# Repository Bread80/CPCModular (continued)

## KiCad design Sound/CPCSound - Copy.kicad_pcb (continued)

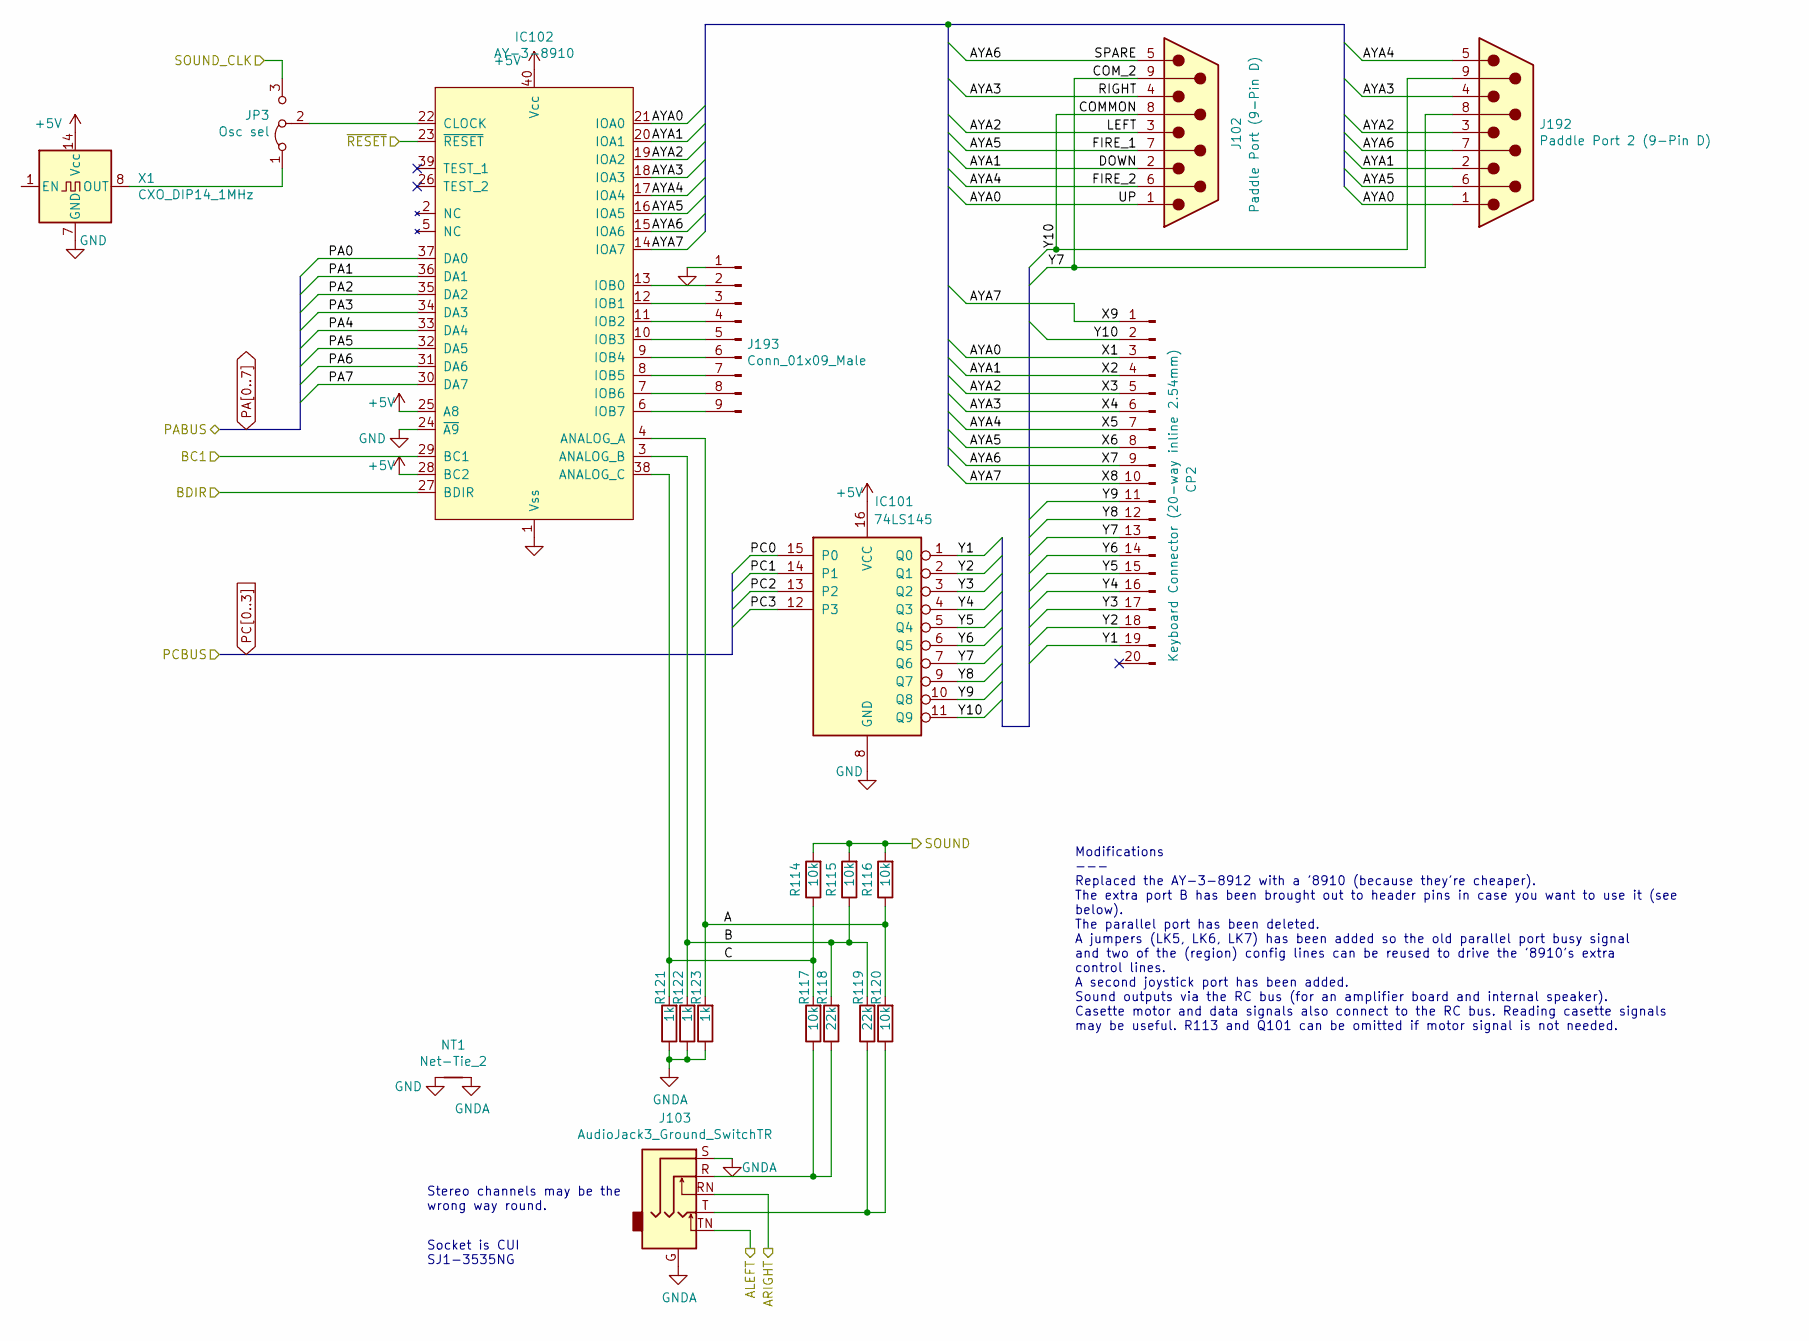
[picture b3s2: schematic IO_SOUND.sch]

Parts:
CP002: Keyboard Connector (20-way inline 2.54mm); PinHeader_1x20_P2.54mm_Vertical
IC101: 74LS145; DIP-16_W7.62mm_Socket
IC102: AY-3-8910; DIP-40_W15.24mm_Socket
J102: Paddle Port (9-Pin D); DSUB-9_Male_Horizontal_P2.77x2.84mm_EdgePinOffset9.90mm_Hou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
J103: AudioJack3_Ground_SwitchTR; Jack_3.5mm_CUI_SJ1-3535NG_Horizontal
J192: Paddle Port 2 (9-Pin D); DSUB-9_Male_Horizontal_P2.77x2.84mm_EdgePinOffset9.40mm
J193: Conn_01x09_Male; PinHeader_1x09_P2.54mm_Vertical
JP3: Osc sel; PinHeader_1x03_P2.54mm_Vertical
NT1: Net-Tie_2; NetTie-2_SMD_Pad0.5mm
R114, R115, R116, R117, R120: 10k; R_Axial_DIN0207_L6.3mm_D2.5mm_P7.62mm_Horizontal
R118, R119: 22k; R_Axial_DIN0207_L6.3mm_D2.5mm_P7.62mm_Horizontal
R121, R122, R123: 1k; R_Axial_DIN0207_L6.3mm_D2.5mm_P7.62mm_Horizontal
X1: CXO_DIP14_1MHz; Oscillator_DIP-14

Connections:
+5V: IC101.16 (VCC), IC102.25 (A8), IC102.28 (BC2), IC102.40 (Vcc), X1.14 (Vcc); also elsewhere on the board
/IO_SOUND/A: IC102.4 (ANALOG_A), R116.1, R120.2, R123.2
/IO_SOUND/ALEFT: J103.TN; also elsewhere on the board
/IO_SOUND/ARIGHT: J103.RN; also elsewhere on the board
/IO_SOUND/AYA0: IC102.21 (IOA0), J102.1, J192.1; also elsewhere on the board
/IO_SOUND/AYA1: IC102.20 (IOA1), J102.2, J192.2; also elsewhere on the board
/IO_SOUND/AYA2: IC102.19 (IOA2), J102.3, J192.3; also elsewhere on the board
/IO_SOUND/AYA3: IC102.18 (IOA3), J102.4, J192.4; also elsewhere on the board
/IO_SOUND/AYA4: IC102.17 (IOA4), J102.6, J192.5; also elsewhere on the board
/IO_SOUND/AYA5: IC102.16 (IOA5), J102.7, J192.6; also elsewhere on the board
/IO_SOUND/AYA6: IC102.15 (IOA6), J102.5, J192.7; also elsewhere on the board
/IO_SOUND/AYA7: IC102.14 (IOA7); also elsewhere on the board
/IO_SOUND/B: IC102.3 (ANALOG_B), R115.1, R118.2, R119.2, R122.2
/IO_SOUND/BC1: IC102.29 (BC1); also elsewhere on the board
/IO_SOUND/BDIR: IC102.27 (BDIR); also elsewhere on the board
/IO_SOUND/C: IC102.38 (ANALOG_C), R114.1, R117.2, R121.2
/IO_SOUND/COMMON: IC101.11 (Q9), J102.8, J192.9; also elsewhere on the board
/IO_SOUND/COM_2: IC101.7 (Q6), J102.9, J192.8; also elsewhere on the board
/IO_SOUND/SOUND: R114.2, R115.2, R116.2; also elsewhere on the board
/IO_SOUND/SOUND_CLK: JP3.3 (B); also elsewhere on the board
/IO_SOUND/Y1: IC101.1 (Q0); also elsewhere on the board
/IO_SOUND/Y2: IC101.2 (Q1); also elsewhere on the board
/IO_SOUND/Y3: IC101.3 (Q2); also elsewhere on the board
/IO_SOUND/Y4: IC101.4 (Q3); also elsewhere on the board
/IO_SOUND/Y5: IC101.5 (Q4); also elsewhere on the board
/IO_SOUND/Y6: IC101.6 (Q5); also elsewhere on the board
/IO_SOUND/Y8: IC101.9 (Q7); also elsewhere on the board
/IO_SOUND/Y9: IC101.10 (Q8); also elsewhere on the board
/IO_SOUND/~RESET: IC102.23 (~RESET); also elsewhere on the board
GND: IC101.8 (GND), IC102.1 (Vss), IC102.24 (~A9), J193.1, NT1.1, X1.7 (GND); also elsewhere on the board
GNDA: J103.G, J103.S, NT1.2, R121.1, R122.1, R123.1
unnamed: IC102.6 (IOB7), J193.9
unnamed: IC102.7 (IOB6), J193.8
unnamed: IC102.8 (IOB5), J193.7
unnamed: IC102.9 (IOB4), J193.6
unnamed: IC102.10 (IOB3), J193.5
unnamed: IC102.11 (IOB2), J193.4
unnamed: IC102.12 (IOB1), J193.3
unnamed: IC102.13 (IOB0), J193.2
unnamed: IC102.22 (CLOCK), JP3.2 (C)
unnamed: J103.R, R117.1, R118.1
unnamed: J103.T, R119.1, R120.1
unnamed: JP3.1 (A), X1.8 (OUT)
PA0: IC102.37 (DA0); also elsewhere on the board
PA1: IC102.36 (DA1); also elsewhere on the board
PA2: IC102.35 (DA2); also elsewhere on the board
PA3: IC102.34 (DA3); also elsewhere on the board
PA4: IC102.33 (DA4); also elsewhere on the board
PA5: IC102.32 (DA5); also elsewhere on the board
PA6: IC102.31 (DA6); also elsewhere on the board
PA7: IC102.30 (DA7); also elsewhere on the board
PC0: IC101.15 (P0); also elsewhere on the board
PC1: IC101.14 (P1); also elsewhere on the board
PC2: IC101.13 (P2); also elsewhere on the board
PC3: IC101.12 (P3); also elsewhere on the board

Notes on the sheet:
Modifications --- Replaced the AY-3-8912 with a '8910 (because they're cheaper). The extra port B has been brought out to header pins in case you want to use it (see below). The parallel port has been deleted. A jumpers (LK5, LK6, LK7) has been added so the old parallel port busy signal and two of 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
Stereo channels may be the wrong way round.
Socket is CUI SJ1-3535NG

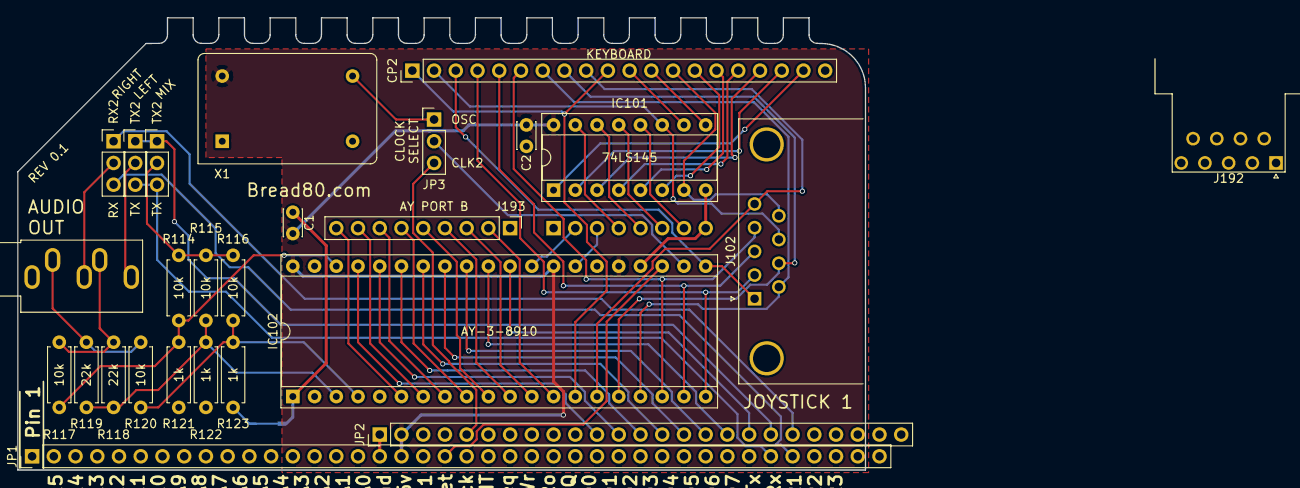
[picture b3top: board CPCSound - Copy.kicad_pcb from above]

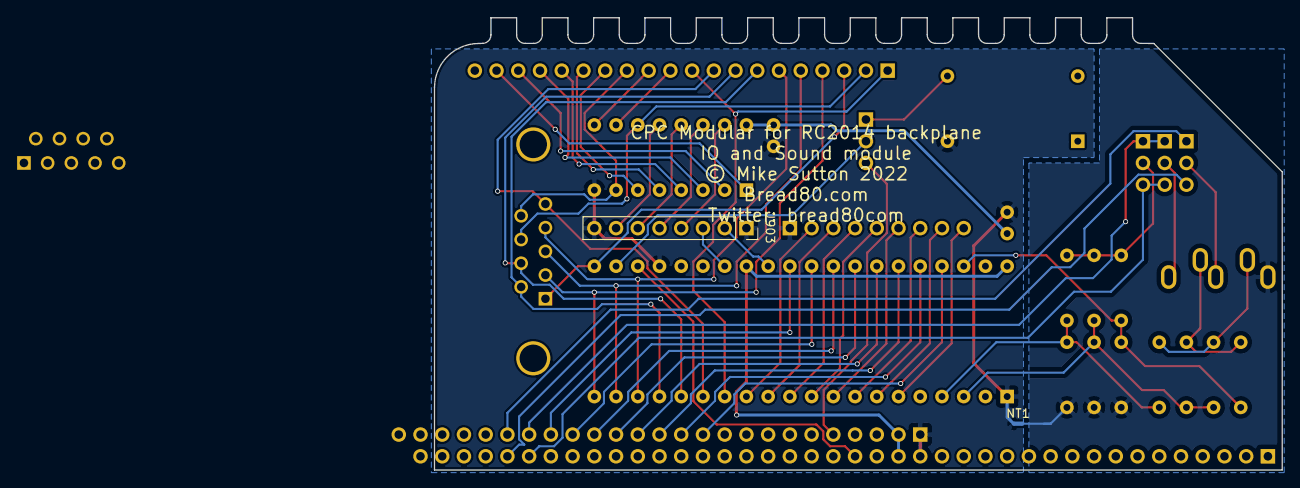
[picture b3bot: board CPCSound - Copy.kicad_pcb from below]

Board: 2 copper layers, 99.1 x 52.9 mm, 28 parts (2 on the bottom side), 59 nets.

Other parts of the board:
CP2: Keyboard Connector (20-way inline 2.54mm); PinHeader_1x20_P2.54mm_Vertical

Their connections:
/IO_SOUND/AYA0: CP2.3; also elsewhere on the board
/IO_SOUND/AYA1: CP2.4; also elsewhere on the board
/IO_SOUND/AYA2: CP2.5; also elsewhere on the board
/IO_SOUND/AYA3: CP2.6; also elsewhere on the board
/IO_SOUND/AYA4: CP2.7; also elsewhere on the board
/IO_SOUND/AYA5: CP2.8; also elsewhere on the board
/IO_SOUND/AYA6: CP2.9; also elsewhere on the board
/IO_SOUND/AYA7: CP2.1, CP2.10; also elsewhere on the board
/IO_SOUND/COMMON: CP2.2; also elsewhere on the board
/IO_SOUND/COM_2: CP2.13; also elsewhere on the board
/IO_SOUND/Y1: CP2.19; also elsewhere on the board
/IO_SOUND/Y2: CP2.18; also elsewhere on the board
/IO_SOUND/Y3: CP2.17; also elsewhere on the board
/IO_SOUND/Y4: CP2.16; also elsewhere on the board
/IO_SOUND/Y5: CP2.15; also elsewhere on the board
/IO_SOUND/Y6: CP2.14; also elsewhere on the board
/IO_SOUND/Y8: CP2.12; also elsewhere on the board
/IO_SOUND/Y9: CP2.11; also elsewhere on the board

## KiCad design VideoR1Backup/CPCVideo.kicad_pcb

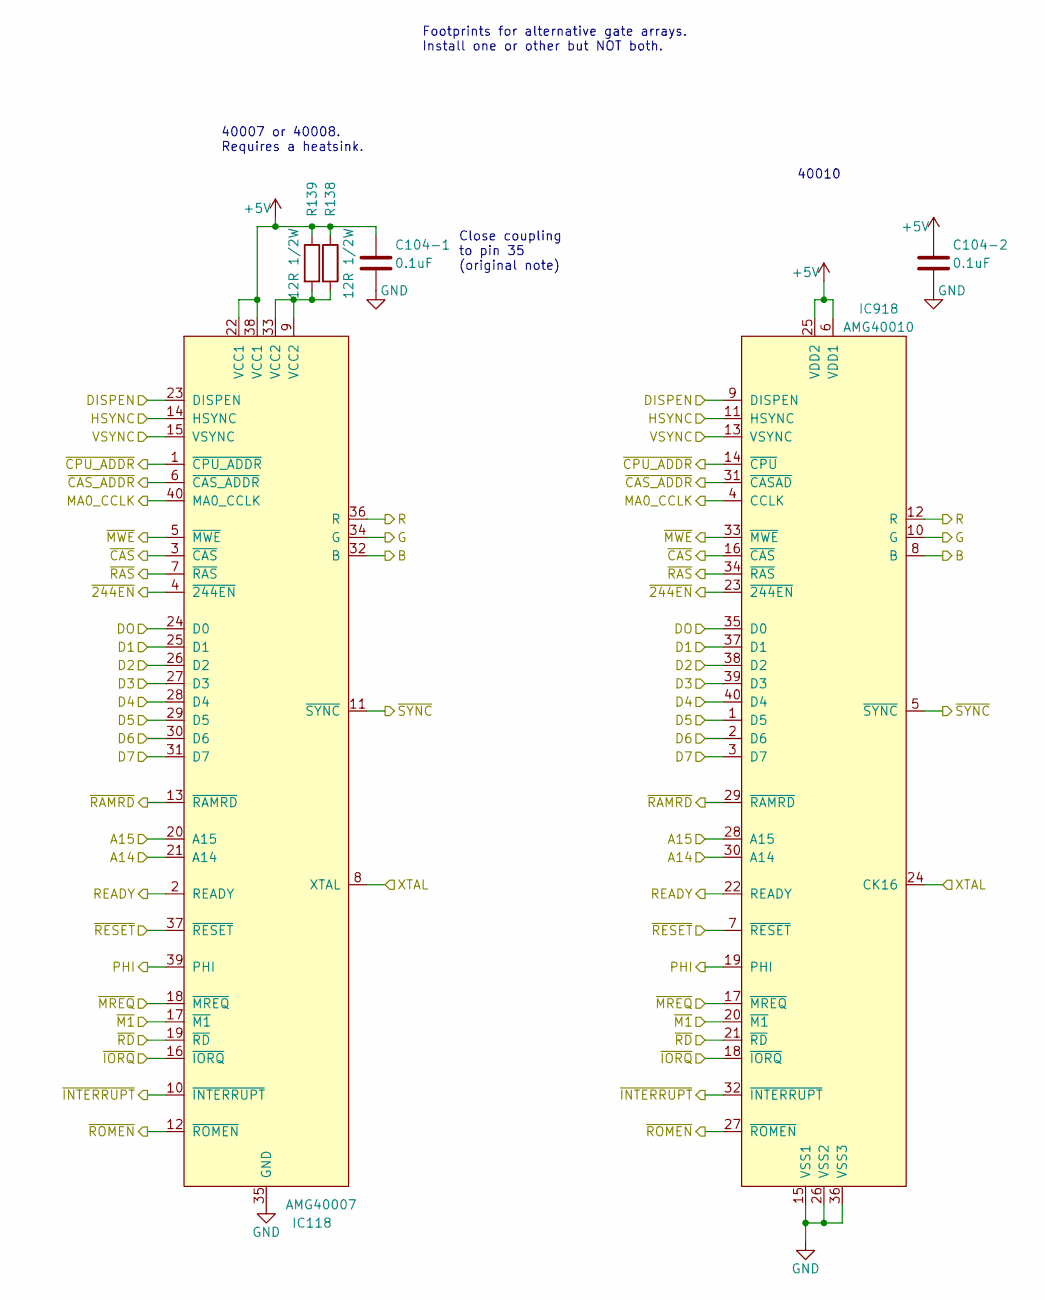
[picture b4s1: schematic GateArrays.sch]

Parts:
C104-1, C104-2: 0.1uF; C_Disc_D3.4mm_W2.1mm_P2.50mm
IC118: AMG40007; DIP-40_W15.24mm_Socket
IC918: AMG40010; DIP-40_W15.24mm_Socket
R138, R139: 12R 1/2W; R_Axial_DIN0309_L9.0mm_D3.2mm_P12.70mm_Horizontal

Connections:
+5V: C104-1.1, C104-2.1, IC118.22 (VCC1), IC118.38 (VCC1), IC918.6 (VDD1), IC918.25 (VDD2), R138.1, R139.1; also elsewhere on the board
/RAM_GA/DISPEN: IC118.23 (DISPEN), IC918.9 (DISPEN); also elsewhere on the board
/RAM_GA/GateArrays/B: IC118.32 (B), IC918.8 (B); also elsewhere on the board
/RAM_GA/GateArrays/G: IC118.34 (G), IC918.10 (G); also elsewhere on the board
/RAM_GA/GateArrays/PHI: IC118.39 (PHI), IC918.19 (PHI); also elsewhere on the board
/RAM_GA/GateArrays/R: IC118.36 (R), IC918.12 (R); also elsewhere on the board
/RAM_GA/GateArrays/XTAL: IC118.8 (XTAL), IC918.24 (CK16); also elsewhere on the board
/RAM_GA/GateArrays/~CAS_ADDR: IC118.6 (~CAS_ADDR), IC918.31 (~CASAD)
/RAM_GA/GateArrays/~SYNC: IC118.11 (~SYNC), IC918.5 (~SYNC); also elsewhere on the board
/RAM_GA/HSYNC: IC118.14 (HSYNC), IC918.11 (HSYNC); also elsewhere on the board
/RAM_GA/MA0_CCLK: IC118.40 (MA0_CCLK), IC918.4 (CCLK); also elsewhere on the board
/RAM_GA/READY: IC118.2 (READY), IC918.22 (READY); also elsewhere on the board
/RAM_GA/VSYNC: IC118.15 (VSYNC), IC918.13 (VSYNC); also elsewhere on the board
/RAM_GA/~244EN: IC118.4 (~244EN), IC918.23 (~244EN); also elsewhere on the board
/RAM_GA/~CAS: IC118.3 (~CAS), IC918.16 (~CAS); also elsewhere on the board
/RAM_GA/~CPU_ADDR: IC118.1 (~CPU_ADDR), IC918.14 (~CPU); also elsewhere on the board
/RAM_GA/~INT: IC118.10 (~INTERRUPT), IC918.32 (~INTERRUPT); also elsewhere on the board
/RAM_GA/~IORQ: IC118.16 (~IORQ), IC918.18 (~IORQ); also elsewhere on the board
/RAM_GA/~M1: IC118.17 (~M1), IC918.20 (~M1); also elsewhere on the board
/RAM_GA/~MREQ: IC118.18 (~MREQ), IC918.17 (~MREQ); also elsewhere on the board
/RAM_GA/~MWE: IC118.5 (~MWE), IC918.33 (~MWE); also elsewhere on the board
/RAM_GA/~RAMRD: IC118.13 (~RAMRD), IC918.29 (~RAMRD); also elsewhere on the board
/RAM_GA/~RAS: IC118.7 (~RAS), IC918.34 (~RAS); also elsewhere on the board
/RAM_GA/~RD: IC118.19 (~RD), IC918.21 (~RD); also elsewhere on the board
/RAM_GA/~RESET: IC118.37 (~RESET), IC918.7 (~RESET); also elsewhere on the board
/RAM_GA/~ROMEN: IC118.12 (~ROMEN), IC918.27 (~ROMEN); also elsewhere on the board
A14: IC118.21 (A14), IC918.30 (A14); also elsewhere on the board
A15: IC118.20 (A15), IC918.28 (A15); also elsewhere on the board
GND: C104-1.2, C104-2.2, IC118.35 (GND), IC918.15 (VSS1), IC918.26 (VSS2), IC918.36 (VSS3); also elsewhere on the board
unnamed: IC118.9 (VCC2), IC118.33 (VCC2), R138.2, R139.2
RD0: IC118.24 (D0), IC918.35 (D0); also elsewhere on the board
RD1: IC118.25 (D1), IC918.37 (D1); also elsewhere on the board
RD2: IC118.26 (D2), IC918.38 (D2); also elsewhere on the board
RD3: IC118.27 (D3), IC918.39 (D3); also elsewhere on the board
RD4: IC118.28 (D4), IC918.40 (D4); also elsewhere on the board
RD5: IC118.29 (D5), IC918.1 (D5); also elsewhere on the board
RD6: IC118.30 (D6), IC918.2 (D6); also elsewhere on the board
RD7: IC118.31 (D7), IC918.3 (D7); also elsewhere on the board

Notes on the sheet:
Close coupling to pin 35 (original note)
40007 or 40008. Requires a heatsink.
40010
Footprints for alternative gate arrays. Install one or other but NOT both.

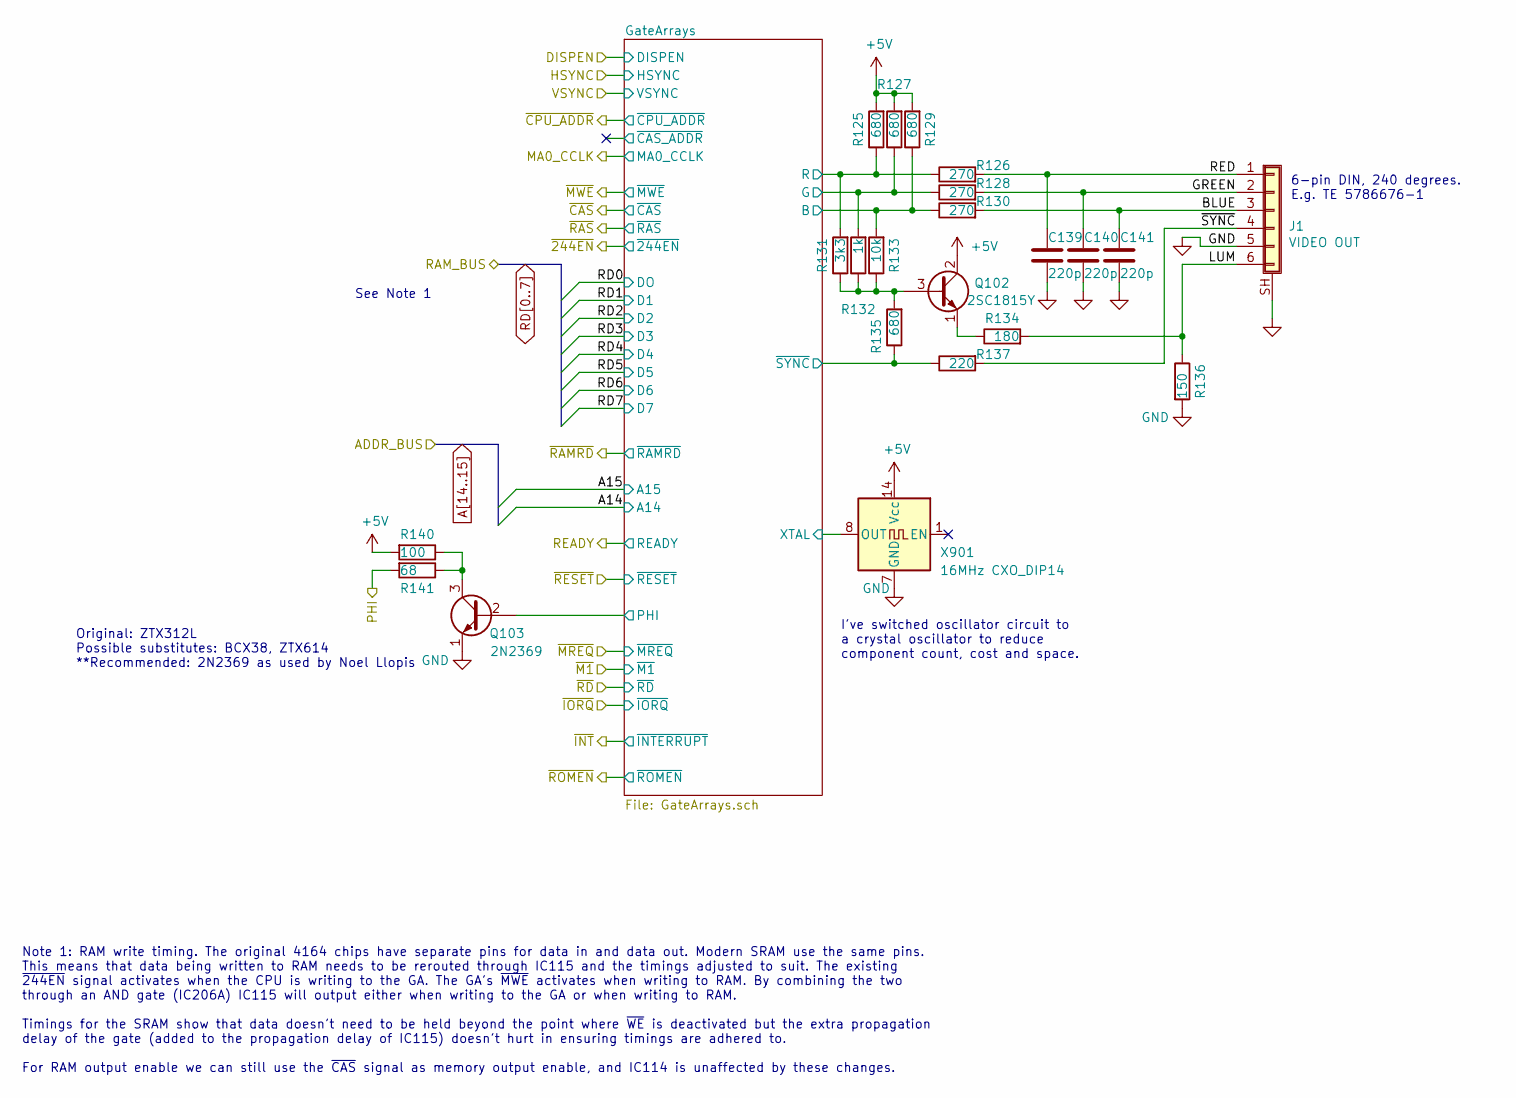
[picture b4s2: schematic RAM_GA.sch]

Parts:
C139, C140, C141: 220p; C_Disc_D3.0mm_W1.6mm_P2.50mm
J1: VIDEO OUT; 6PinDIN240Degree
Q102: 2SC1815Y; TO-92_HandSolder
Q103: 2N2369; TO-18-3
R125, R127, R129, R135: 680; R_Axial_DIN0207_L6.3mm_D2.5mm_P7.62mm_Horizontal
R126, R128, R130: 270; R_Axial_DIN0207_L6.3mm_D2.5mm_P7.62mm_Horizontal
R131: 3k3; R_Axial_DIN0207_L6.3mm_D2.5mm_P7.62mm_Horizontal
R132: 1k; R_Axial_DIN0207_L6.3mm_D2.5mm_P7.62mm_Horizontal
R133: 10k; R_Axial_DIN0207_L6.3mm_D2.5mm_P7.62mm_Horizontal
R134: 180; R_Axial_DIN0207_L6.3mm_D2.5mm_P7.62mm_Horizontal
R136: 150; R_Axial_DIN0207_L6.3mm_D2.5mm_P7.62mm_Horizontal
R137: 220; R_Axial_DIN0207_L6.3mm_D2.5mm_P7.62mm_Horizontal
R140: 100; R_Axial_DIN0207_L6.3mm_D2.5mm_P7.62mm_Horizontal
R141: 68; R_Axial_DIN0207_L6.3mm_D2.5mm_P7.62mm_Horizontal
X201: 16MHz CXO_DIP14; Oscillator_DIP-14

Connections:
+5V: Q102.2 (C), R125.2, R127.2, R129.2, R140.2; also elsewhere on the board
/RAM_GA/BLUE: C141.1, J1.3, R130.2
/RAM_GA/GREEN: C140.1, J1.2, R128.2
/RAM_GA/GateArrays/B: R129.1, R130.1, R133.2; also elsewhere on the board
/RAM_GA/GateArrays/G: R127.1, R128.1, R132.2; also elsewhere on the board
/RAM_GA/GateArrays/PHI: Q103.2 (B); also elsewhere on the board
/RAM_GA/GateArrays/R: R125.1, R126.1, R131.2; also elsewhere on the board
/RAM_GA/GateArrays/~SYNC: R135.1, R137.1; also elsewhere on the board
/RAM_GA/LUM: J1.6, R134.2, R136.1
/RAM_GA/PHI: R141.2; also elsewhere on the board
/RAM_GA/RED: C139.1, J1.1, R126.2
/RAM_GA/~SYNC: J1.4, R137.2
GND: C139.2, C140.2, C141.2, J1.5, J1.SH (Shield), Q103.1 (E), R136.2; also elsewhere on the board
unnamed: Q102.1 (E), R134.1
unnamed: Q102.3 (B), R131.1, R132.1, R133.1, R135.2
unnamed: Q103.3 (C), R140.1, R141.1

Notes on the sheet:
See Note 1
Note 1: RAM write timing. The original 4164 chips have separate pins for data in and data out. Modern SRAM use the same pins. This means that data being written to RAM needs to be rerouted through IC115 and the timings adjusted to suit. The existing ~244EN~ signal activates when the CPU is writing 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
I've switched oscillator circuit to a crystal oscillator to reduce component count, cost and space.
Original: ZTX312L Possible substitutes: BCX38, ZTX614 **Recommended: 2N2369 as used by Noel Llopis
6-pin DIN, 240 degrees. E.g. TE 5786676-1

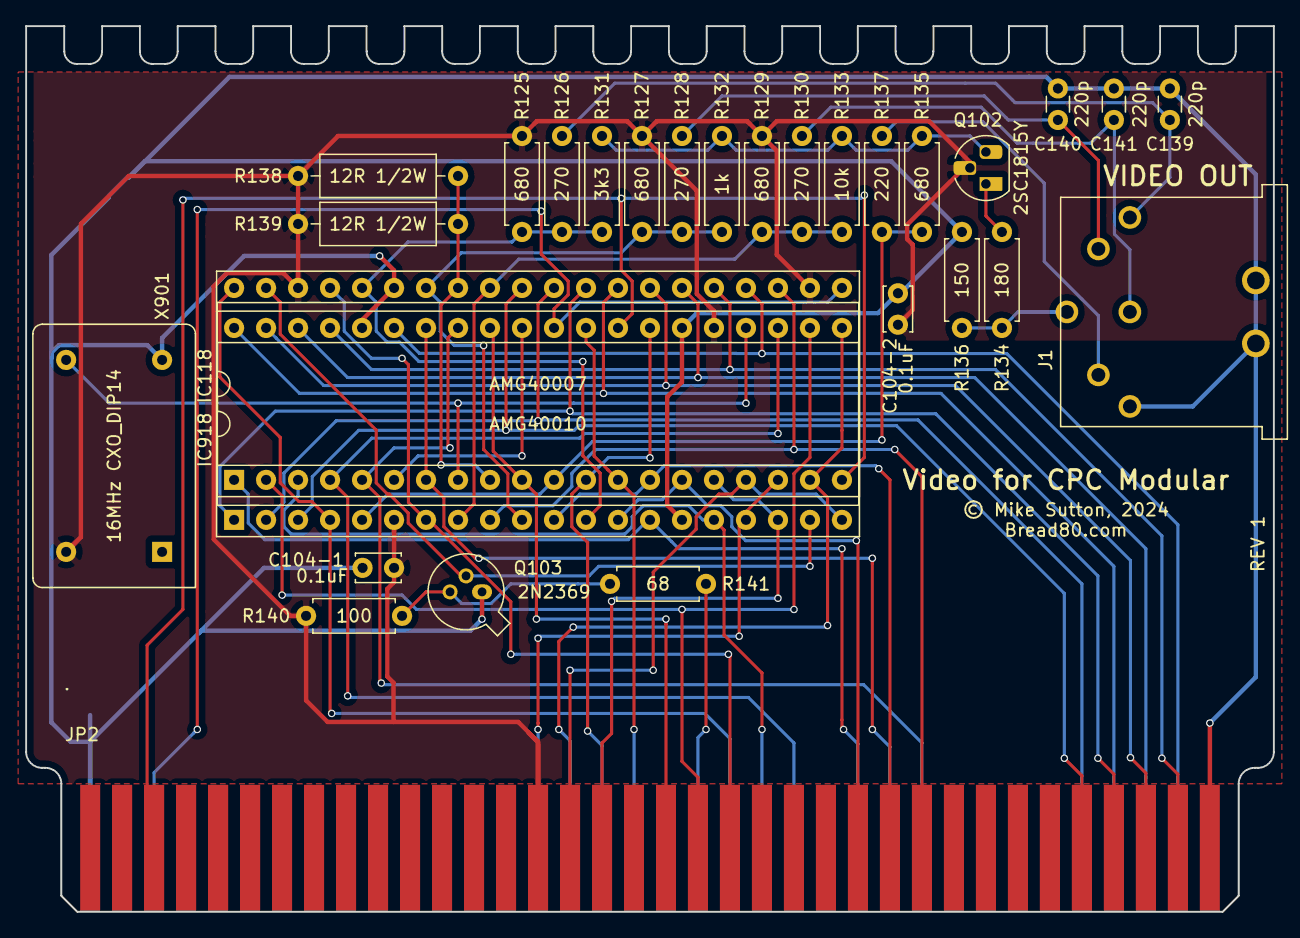
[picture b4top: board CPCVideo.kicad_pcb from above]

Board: 2 copper layers, 99.1 x 70.3 mm, 30 parts (1 on the bottom side), 47 nets.

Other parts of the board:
JP1: CPCM_VideoRAM_EdgeBottom; Edge36_2.54PS
JP2: CPCM_VideoRAM_EdgeTop; Edge36_2.54PS
X901: 16MHz CXO_DIP14; Oscillator_DIP-14

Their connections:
+5V: JP2.15, X901.14; also elsewhere on the board
/RAM_GA/DISPEN: JP2.27; also elsewhere on the board
/RAM_GA/GateArrays/XTAL: X901.8; also elsewhere on the board
/RAM_GA/HSYNC: JP2.26; also elsewhere on the board
/RAM_GA/MA0_CCLK: JP1.21; also elsewhere on the board
/RAM_GA/PHI: JP1.20; also elsewhere on the board
/RAM_GA/READY: JP2.20; also elsewhere on the board
/RAM_GA/VSYNC: JP2.25; also elsewhere on the board
/RAM_GA/~244EN: JP1.23; also elsewhere on the board
/RAM_GA/~CAS: JP1.22; also elsewhere on the board
/RAM_GA/~CPU_ADDR: JP1.25; also elsewhere on the board
/RAM_GA/~INT: JP2.19; also elsewhere on the board
/RAM_GA/~IORQ: JP2.17; also elsewhere on the board
/RAM_GA/~M1: JP2.16; also elsewhere on the board
/RAM_GA/~MREQ: JP1.15; also elsewhere on the board
/RAM_GA/~MWE: JP1.27; also elsewhere on the board
/RAM_GA/~RAMRD: JP1.18; also elsewhere on the board
/RAM_GA/~RAS: JP1.26; also elsewhere on the board
/RAM_GA/~RD: JP1.16; also elsewhere on the board
/RAM_GA/~RESET: JP2.21; also elsewhere on the board
/RAM_GA/~ROMEN: JP1.17; also elsewhere on the board
A14: JP1.3; also elsewhere on the board
A15: JP2.3; also elsewhere on the board
GND: JP1.1, JP2.36, X901.7; also elsewhere on the board
RD0: JP1.35; also elsewhere on the board
RD1: JP2.35; also elsewhere on the board
RD2: JP1.34; also elsewhere on the board
RD3: JP2.34; also elsewhere on the board
RD4: JP1.33; also elsewhere on the board
RD5: JP2.33; also elsewhere on the board
RD6: JP1.32; also elsewhere on the board
RD7: JP2.32; also elsewhere on the board
